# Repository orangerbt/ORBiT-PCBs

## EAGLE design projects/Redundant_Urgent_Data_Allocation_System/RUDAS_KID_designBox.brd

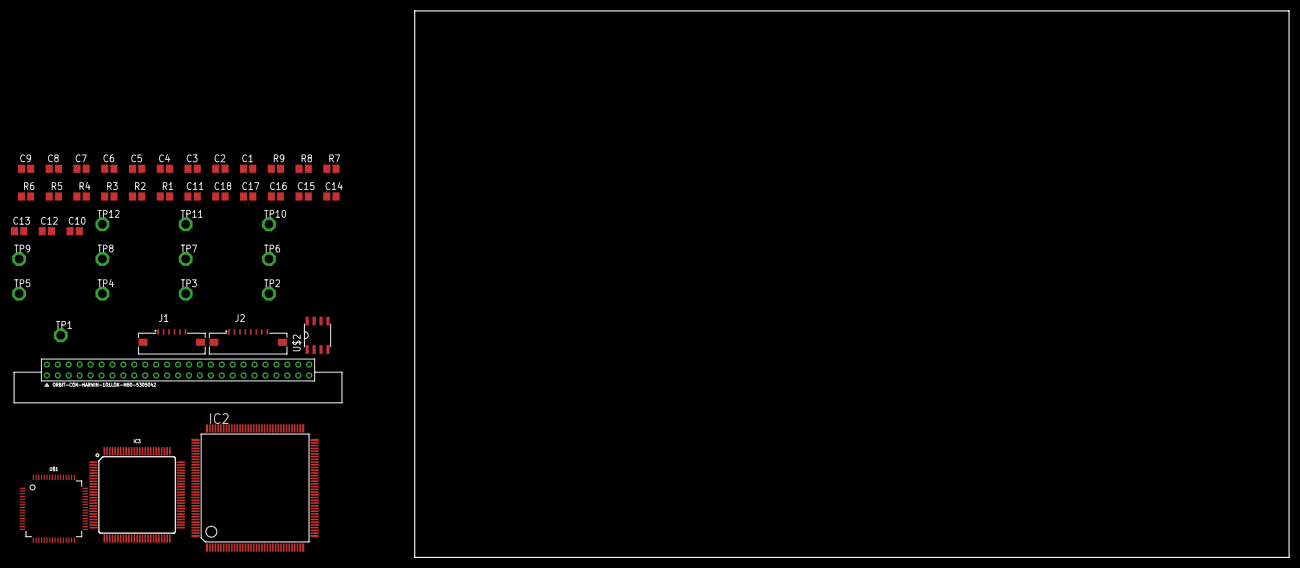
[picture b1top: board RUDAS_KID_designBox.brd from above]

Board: 2 copper layers, 160.0 x 100.0 mm, 46 parts (0 on the bottom side), 100 nets, no tracks yet.

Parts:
C1, C2, C3, C4, C5, C6, C7, C8, C9, C10, C11, C12, C13, C14, C15, C16, C17, C18: C2012
IC2: STM32F103VGT6; LQFP144
IC3: 5M240ZT100; TQFP100
J1: 686106183522
J2: 686108183422
R1, R2, R3, R4, R5, R6, R7, R8, R9: R2012
TP1, TP2, TP3, TP4, TP5, TP6, TP7, TP8, TP9, TP10, TP11, TP12: TP063; TP_063
U$1: IDT71V30; TQFP64
U$2: ISO1050; SOP8
U$5: CARD_EDGE_50PINM80-5305042; M80-5305042

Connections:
!BUSY!: IC3.77, U$1.60
!CE!: IC3.75, U$1.58
!INT!: IC3.76, U$1.61
!OE!: IC3.74, U$1.1
A0: IC3.73, U$1.2
A1: IC3.72, U$1.3
A2: IC3.71, U$1.4
A3: IC3.70, U$1.5
A4: IC3.69, U$1.6
A5: IC3.68, U$1.7
A6: IC3.67, U$1.8
A7: IC3.66, U$1.10
A8: IC3.64, U$1.11
A9: IC3.62, U$1.12
CPLD_GND: C3.2, C4.2, C5.2, C6.2, C7.2, C8.2, C9.2, C10.2, IC3.1, IC3.10, IC3.11, IC3.32, IC3.46, IC3.60, IC3.65, IC3.79, IC3.93, J1.1, R9.1
CPLD_IO_VCC: J1.6, R6.2, R7.2, R8.2
CPLD_VCC: C3.1, C4.1, C5.1, C6.1, C7.1, C8.1, C9.1, C10.1
CPLD_VCC_CORE: IC3.13, IC3.63
CPLD_VCC_IO2: IC3.59, IC3.80, IC3.94
CPL_VCC_IO1: IC3.9, IC3.31, IC3.45
C_TCK: IC3.24, J1.5, R9.2
C_TDI: IC3.23, J1.2, R8.1
C_TDO: IC3.25, J1.4, R6.1
C_TMS: IC3.22, J1.3, R7.1
D0: IC3.58, U$1.14
D1: IC3.57, U$1.15
D2: IC3.56, U$1.16
D3: IC3.55, U$1.17
D4: IC3.54, U$1.19
D5: IC3.53, U$1.20
D6: IC3.52, U$1.21
D7: IC3.51, U$1.22
FSMC_!NE1!: IC2.123, U$1.55
FSMC_!NOE!: IC2.118, U$1.48
FSMC_A0: IC2.10, U$1.47
FSMC_A1: IC2.11, U$1.46
FSMC_A2: IC2.12, U$1.45
FSMC_A3: IC2.13, U$1.44
FSMC_A4: IC2.14, U$1.43
FSMC_A5: IC2.15, U$1.42
FSMC_A6: IC2.50, U$1.41
FSMC_A7: IC2.53, U$1.39
FSMC_A8: IC2.54, U$1.38
FSMC_A9: IC2.55, U$1.37
FSMC_D0: IC2.85, U$1.26
FSMC_D1: IC2.86, U$1.27
FSMC_D2: IC2.114, U$1.28
FSMC_D3: IC2.115, U$1.29
FSMC_D4: IC2.58, U$1.31
FSMC_D5: IC2.59, U$1.32
FSMC_D6: IC2.60, U$1.33
FSMC_D7: IC2.63, U$1.34
LAN_CLK_N0: IC3.81, U$5.PIN9
LAN_CLK_N1: IC3.85, U$5.PIN15
LAN_CLK_N2: IC3.96, U$5.PIN21
LAN_CLK_N3: IC3.29, U$5.PIN34
LAN_CLK_N4: IC3.19, U$5.PIN40
LAN_CLK_N5: IC3.5, U$5.PIN46
LAN_CLK_P0: IC3.82, U$5.PIN10
LAN_CLK_P1: IC3.86, U$5.PIN16
LAN_CLK_P2: IC3.97, U$5.PIN22
LAN_CLK_P3: IC3.28, U$5.PIN35
LAN_CLK_P4: IC3.18, U$5.PIN41
LAN_CLK_P5: IC3.4, U$5.PIN47
LAN_N0: IC3.83, U$5.PIN11
LAN_N1: IC3.87, U$5.PIN17
LAN_N2: IC3.98, U$5.PIN23
LAN_N3: IC3.27, U$5.PIN36
LAN_N4: IC3.17, U$5.PIN42
LAN_N5: IC3.3, U$5.PIN48
LAN_P0: IC3.84, U$5.PIN12
LAN_P1: IC3.88, U$5.PIN18
LAN_P2: IC3.99, U$5.PIN24
LAN_P3: IC3.26, U$5.PIN37
LAN_P4: IC3.16, U$5.PIN43
LAN_P5: IC3.2, U$5.PIN49
unnamed: C1.1, C2.1, U$1.56, U$1.57
unnamed: C1.2, C2.2, U$1.24, U$1.25
R/!W!: IC3.78, U$1.59
SIGNAL_GND: U$5.PIN8, U$5.PIN14, U$5.PIN20, U$5.PIN33, U$5.PIN39, U$5.PIN45
STM32_CAN_RX: IC2.103, TP7.TP, U$2.2
STM32_CAN_TX: IC2.104, TP8.TP, U$2.3
STM32_I2C1_SCL: IC2.136, TP9.TP
STM32_I2C1_SDA: IC2.137, TP10.TP
STM32_SPI1_CS: IC2.40, TP1.TP
STM32_SPI1_MISO: IC2.42, TP3.TP
STM32_SPI1_MOSI: IC2.43, TP4.TP
STM32_SPI1_SCK: IC2.41, TP2.TP
STM32_UART1_RX: IC2.102, TP6.TP
STM32_UART1_TX: IC2.101, TP5.TP
STM32_UART2_RX: IC2.36, TP12.TP
STM32_UART2_TX: IC2.35, TP11.TP
S_GND: C11.2, C12.2, C13.2, C14.2, C15.2, C16.2, C17.2, C18.2, IC2.16, IC2.38, IC2.51, IC2.61, IC2.71, IC2.83, IC2.94, IC2.107, IC2.120, IC2.130, IC2.143, J2.1, R5.1, U$2.4
S_RST: IC2.25, J2.2
S_TCK: IC2.109, J2.4, R5.2
S_TDI: IC2.110, J2.6, R2.1
S_TDO: IC2.133, J2.3, R4.1
S_TMS: IC2.105, J2.5, R3.1
S_TRST: IC2.134, J2.7, R1.1
S_VCC: C11.1, C12.1, C13.1, C14.1, C15.1, C16.1, C17.1, C18.1, IC2.17, IC2.39, IC2.52, IC2.62, IC2.72, IC2.84, IC2.95, IC2.108, IC2.121, IC2.131, IC2.144, J2.8, R1.2, R2.2, R3.2, R4.2, U$2.1

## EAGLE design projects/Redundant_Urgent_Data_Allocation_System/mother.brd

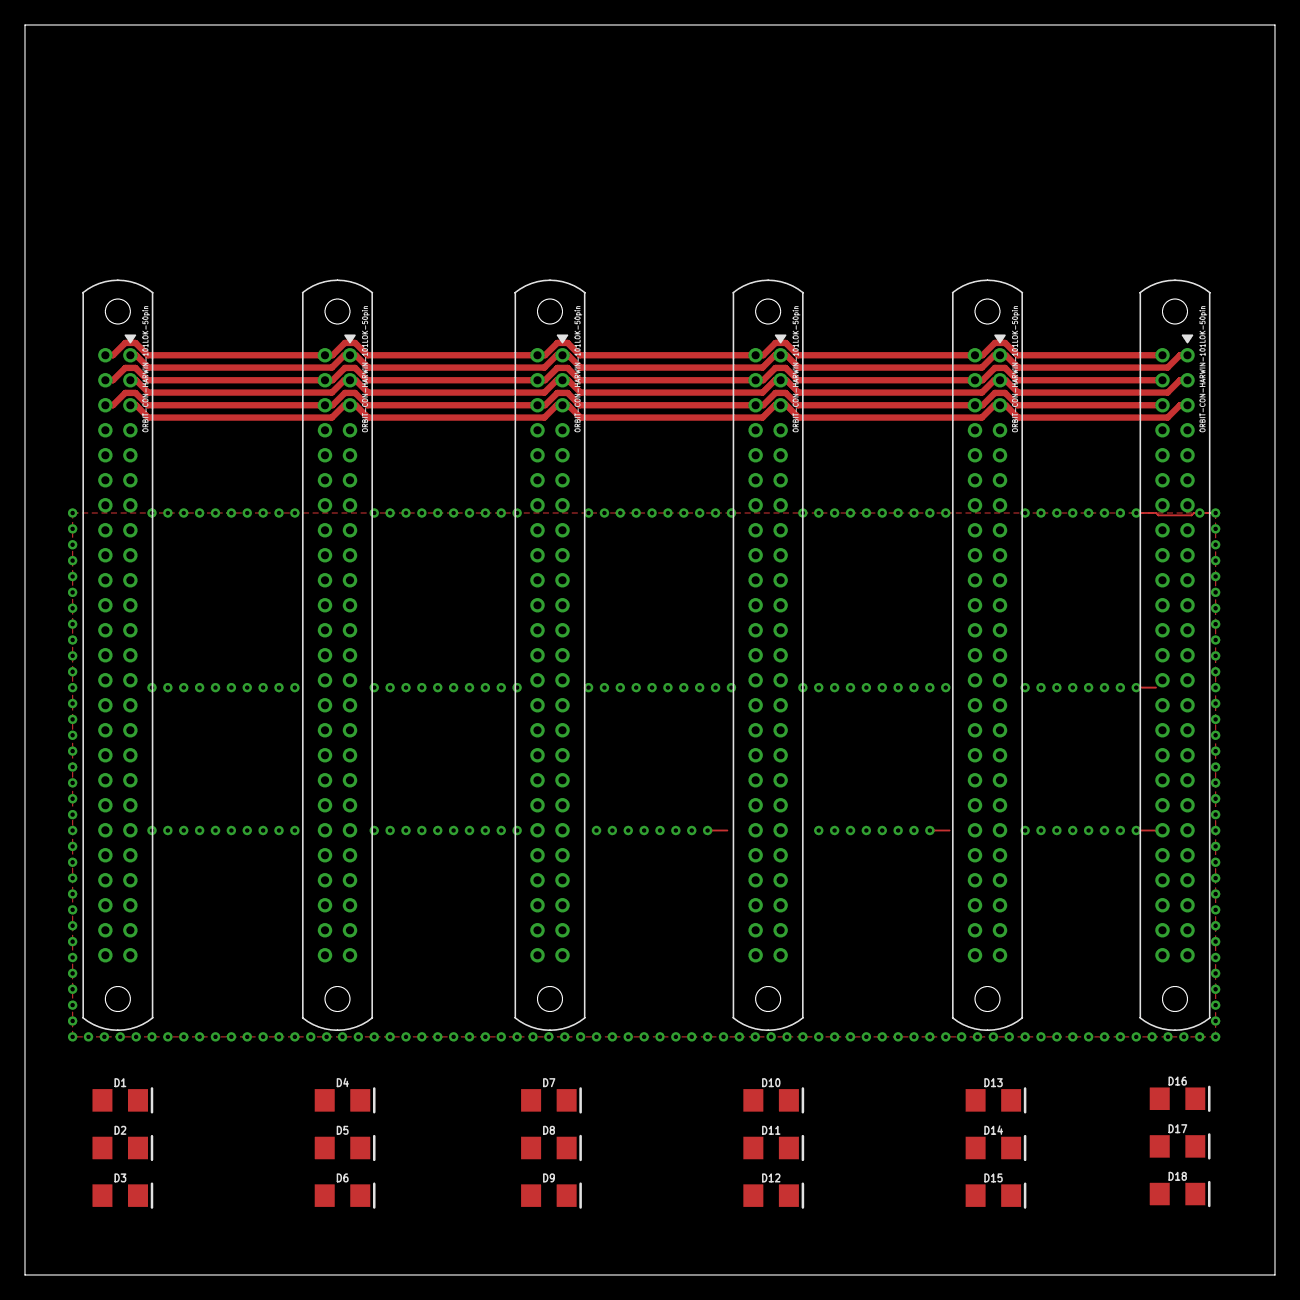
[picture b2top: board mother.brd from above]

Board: 4 copper layers, 100.0 x 100.0 mm, 24 parts (0 on the bottom side), 41 nets.

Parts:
D1, D2, D3, D4, D5, D6, D7, D8, D9, D10, D11, D12, D13, D14, D15, D16, D17, D18: FKIT-LED-1206
U$1, U$2, U$3, U$4, U$5, U$6: CARD_EDGE_50PINM80-4115042; M80-4115042

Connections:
3V_GND: U$1.PIN28, U$2.PIN28, U$3.PIN28, U$4.PIN28, U$5.PIN28, U$6.PIN28
5V_GND: U$1.PIN2, U$2.PIN2, U$3.PIN2, U$4.PIN2, U$5.PIN2, U$6.PIN2
12V_GND: U$1.PIN26, U$2.PIN26, U$3.PIN26, U$4.PIN26, U$5.PIN26, U$6.PIN26
+3V: U$1.PIN3, U$2.PIN3, U$3.PIN3, U$4.PIN3, U$5.PIN3, U$6.PIN3
+5V: U$1.PIN27, U$2.PIN27, U$3.PIN27, U$4.PIN27, U$5.PIN27, U$6.PIN27
+12V: U$1.PIN1, U$2.PIN1, U$3.PIN1, U$4.PIN1, U$5.PIN1, U$6.PIN1
CAN_H_P: U$1.PIN4, U$2.PIN4, U$3.PIN4, U$4.PIN4, U$5.PIN4, U$6.PIN4
CAN_H_S: U$1.PIN29, U$2.PIN29, U$3.PIN29, U$4.PIN29, U$5.PIN29, U$6.PIN29
CAN_L_P: U$1.PIN5, U$2.PIN5, U$3.PIN5, U$4.PIN5, U$5.PIN5, U$6.PIN5
CAN_L_S: U$1.PIN30, U$2.PIN30, U$3.PIN30, U$4.PIN30, U$5.PIN30, U$6.PIN30
LAN_CLK_N0: U$1.PIN9, U$2.PIN9, U$3.PIN9, U$4.PIN9, U$5.PIN9, U$6.PIN9
LAN_CLK_N1: U$1.PIN15, U$2.PIN15, U$3.PIN15, U$4.PIN15, U$5.PIN15, U$6.PIN15
LAN_CLK_N2: U$1.PIN21, U$2.PIN21, U$3.PIN21, U$4.PIN21, U$5.PIN21, U$6.PIN21
LAN_CLK_N3: U$1.PIN34, U$2.PIN34, U$3.PIN34, U$4.PIN34, U$5.PIN34, U$6.PIN34
LAN_CLK_N4: U$1.PIN40, U$2.PIN40, U$3.PIN40, U$4.PIN40, U$5.PIN40, U$6.PIN40
LAN_CLK_N5: U$1.PIN46, U$2.PIN46, U$3.PIN46, U$4.PIN46, U$5.PIN46, U$6.PIN46
LAN_CLK_P0: U$1.PIN10, U$2.PIN10, U$3.PIN10, U$4.PIN10, U$5.PIN10, U$6.PIN10
LAN_CLK_P1: U$1.PIN16, U$2.PIN16, U$3.PIN16, U$4.PIN16, U$5.PIN16, U$6.PIN16
LAN_CLK_P2: U$1.PIN22, U$2.PIN22, U$3.PIN22, U$4.PIN22, U$5.PIN22, U$6.PIN22
LAN_CLK_P3: U$1.PIN35, U$2.PIN35, U$3.PIN35, U$4.PIN35, U$5.PIN35, U$6.PIN35
LAN_CLK_P4: U$1.PIN41, U$2.PIN41, U$3.PIN41, U$4.PIN41, U$5.PIN41, U$6.PIN41
LAN_CLK_P5: U$1.PIN47, U$2.PIN47, U$3.PIN47, U$4.PIN47, U$5.PIN47, U$6.PIN47
LAN_N0: U$1.PIN11, U$2.PIN11, U$3.PIN11, U$4.PIN11, U$5.PIN11, U$6.PIN11
LAN_N1: U$1.PIN17, U$2.PIN17, U$3.PIN17, U$4.PIN17, U$5.PIN17, U$6.PIN17
LAN_N2: U$1.PIN23, U$2.PIN23, U$3.PIN23, U$4.PIN23, U$5.PIN23, U$6.PIN23
LAN_N3: U$1.PIN36, U$2.PIN36, U$3.PIN36, U$4.PIN36, U$5.PIN36, U$6.PIN36
LAN_N4: U$1.PIN42, U$2.PIN42, U$3.PIN42, U$4.PIN42, U$5.PIN42, U$6.PIN42
LAN_N5: U$1.PIN48, U$2.PIN48, U$3.PIN48, U$4.PIN48, U$5.PIN48, U$6.PIN48
LAN_P0: U$1.PIN12, U$2.PIN12, U$3.PIN12, U$4.PIN12, U$5.PIN12, U$6.PIN12
LAN_P1: U$1.PIN18, U$2.PIN18, U$3.PIN18, U$4.PIN18, U$5.PIN18, U$6.PIN18
LAN_P2: U$1.PIN24, U$2.PIN24, U$3.PIN24, U$4.PIN24, U$5.PIN24, U$6.PIN24
LAN_P3: U$1.PIN37, U$2.PIN37, U$3.PIN37, U$4.PIN37, U$5.PIN37, U$6.PIN37
LAN_P4: U$1.PIN43, U$2.PIN43, U$3.PIN43, U$4.PIN43, U$5.PIN43, U$6.PIN43
LAN_P5: U$1.PIN49, U$2.PIN49, U$3.PIN49, U$4.PIN49, U$5.PIN49, U$6.PIN49
NOTE0: U$1.PIN13, U$2.PIN13, U$3.PIN13, U$4.PIN13, U$5.PIN13, U$6.PIN13
NOTE1: U$1.PIN19, U$2.PIN19, U$3.PIN19, U$4.PIN19, U$5.PIN19, U$6.PIN19
NOTE2: U$1.PIN25, U$2.PIN25, U$3.PIN25, U$4.PIN25, U$5.PIN25, U$6.PIN25
NOTE3: U$1.PIN38, U$2.PIN38, U$3.PIN38, U$4.PIN38, U$5.PIN38, U$6.PIN38
NOTE4: U$1.PIN44, U$2.PIN44, U$3.PIN44, U$4.PIN44, U$5.PIN44, U$6.PIN44
NOTE5: U$1.PIN50, U$2.PIN50, U$3.PIN50, U$4.PIN50, U$5.PIN50, U$6.PIN50
SIGNAL_GND: U$1.PIN8, U$1.PIN14, U$1.PIN20, U$1.PIN33, U$1.PIN39, U$1.PIN45, U$2.PIN8, U$2.PIN14, U$2.PIN20, U$2.PIN33, U$2.PIN39, U$2.PIN45, U$3.PIN8, U$3.PIN14, U$3.PIN20, U$3.PIN33, U$3.PIN39, U$3.PIN45, U$4.PIN8, U$4.PIN14, U$4.PIN20, U$4.PIN33, U$4.PIN39, U$4.PIN45, U$5.PIN8, U$5.PIN14, U$5.PIN20, U$5.PIN33, U$5.PIN39, U$5.PIN45, U$6.PIN8, U$6.PIN14, U$6.PIN20, U$6.PIN33, U$6.PIN39, U$6.PIN45

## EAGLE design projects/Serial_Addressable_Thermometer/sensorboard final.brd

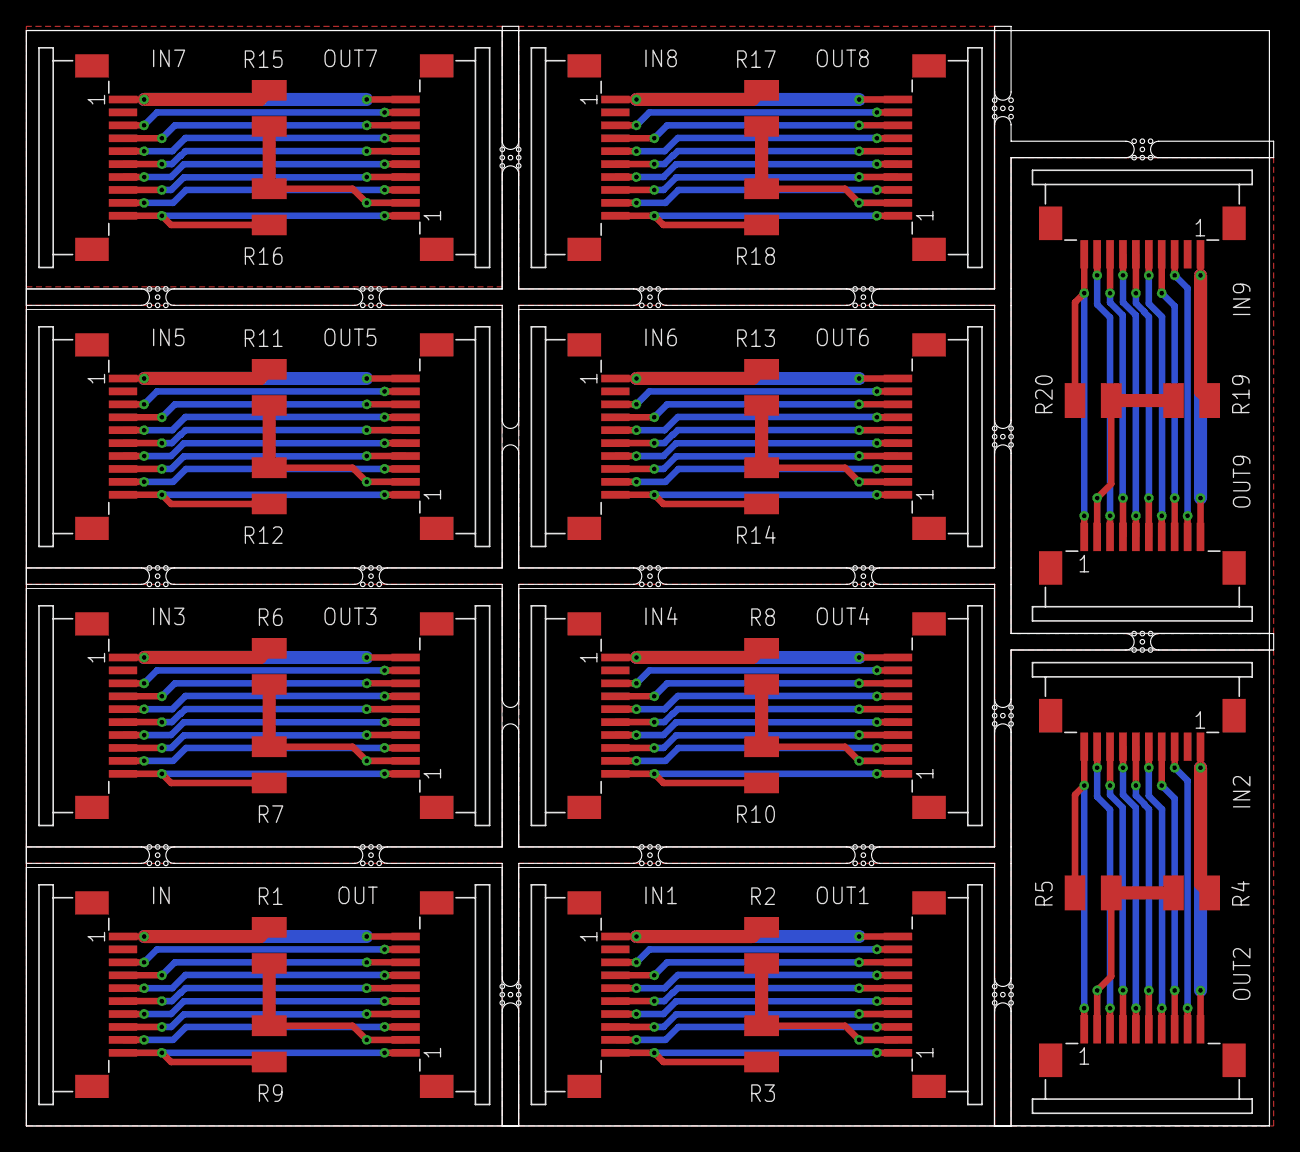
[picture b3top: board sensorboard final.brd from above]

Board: 2 copper layers, 96.2 x 84.8 mm, 40 parts (0 on the bottom side), 100 nets.

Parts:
IN, IN1, IN2, IN3, IN4, IN5, IN6, IN7, IN8, IN9: analog; 68611014422
OUT, OUT1, OUT2, OUT3, OUT4, OUT5, OUT6, OUT7, OUT8, OUT9: analog; 68611014422
R1, R2, R4, R6, R8, R11, R13, R15, R17, R19: NTC; R1210
R3, R5, R7, R9, R10, R12, R14, R16, R18, R20: 10K; R1210

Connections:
+5V: IN.1, OUT.10, R1.2
+5V1: IN1.1, OUT1.10, R2.2
+5V2: IN2.1, OUT2.10, R4.2
+5V3: IN3.1, OUT3.10, R6.2
+5V4: IN4.1, OUT4.10, R8.2
+5V5: IN5.1, OUT5.10, R11.2
+5V6: IN6.1, OUT6.10, R13.2
+5V7: IN7.1, OUT7.10, R15.2
+5V8: IN8.1, OUT8.10, R17.2
+5V9: IN9.1, OUT9.10, R19.2
AD1: IN1.3, OUT1.9
AD2: IN.3, OUT.9
AD3: IN.4, OUT.8
AD4: IN.5, OUT.7
AD5: IN.6, OUT.6
AD6: IN.7, OUT.5
AD7: IN.8, OUT.4
AD8: IN.9, OUT.3
AD9: IN1.4, OUT1.8
AD10: IN1.5, OUT1.7
AD11: IN1.9, OUT1.3
AD12: IN1.8, OUT1.4
AD13: IN1.7, OUT1.5
AD14: IN1.6, OUT1.6
AD15: IN2.3, OUT2.9
AD16: IN2.4, OUT2.8
AD17: IN2.5, OUT2.7
AD18: IN2.9, OUT2.3
AD19: IN2.8, OUT2.4
AD20: IN2.7, OUT2.5
AD21: IN2.6, OUT2.6
AD22: IN3.3, OUT3.9
AD23: IN3.4, OUT3.8
AD24: IN3.5, OUT3.7
AD25: IN3.9, OUT3.3
AD26: IN3.8, OUT3.4
AD27: IN3.7, OUT3.5
AD28: IN3.6, OUT3.6
AD29: IN4.3, OUT4.9
AD30: IN4.4, OUT4.8
AD31: IN4.5, OUT4.7
AD32: IN4.9, OUT4.3
AD33: IN4.8, OUT4.4
AD34: IN4.7, OUT4.5
AD35: IN4.6, OUT4.6
AD36: IN5.3, OUT5.9
AD37: IN5.4, OUT5.8
AD38: IN5.5, OUT5.7
AD39: IN5.9, OUT5.3
AD40: IN5.8, OUT5.4
AD41: IN5.7, OUT5.5
AD42: IN5.6, OUT5.6
AD43: IN6.3, OUT6.9
AD44: IN6.4, OUT6.8
AD45: IN6.5, OUT6.7
AD46: IN6.9, OUT6.3
AD47: IN6.8, OUT6.4
AD48: IN6.7, OUT6.5
AD49: IN6.6, OUT6.6
AD50: IN7.3, OUT7.9
AD51: IN7.4, OUT7.8
AD52: IN7.5, OUT7.7
AD53: IN7.9, OUT7.3
AD54: IN7.8, OUT7.4
AD55: IN7.7, OUT7.5
AD56: IN7.6, OUT7.6
AD57: IN8.3, OUT8.9
AD58: IN8.4, OUT8.8
AD59: IN8.5, OUT8.7
AD60: IN8.9, OUT8.3
AD61: IN8.8, OUT8.4
AD62: IN8.7, OUT8.5
AD63: IN8.6, OUT8.6
AD64: IN9.3, OUT9.9
AD65: IN9.4, OUT9.8
AD66: IN9.5, OUT9.7
AD67: IN9.9, OUT9.3
AD68: IN9.8, OUT9.4
AD69: IN9.7, OUT9.5
AD70: IN9.6, OUT9.6
ADB: OUT.2, R1.1, R9.2
ADB1: OUT1.2, R2.1, R3.2
ADB2: OUT2.2, R4.1, R5.2
ADB3: OUT3.2, R6.1, R7.2
ADB4: OUT4.2, R8.1, R10.2
ADB5: OUT5.2, R11.1, R12.2
ADB6: OUT6.2, R13.1, R14.2
ADB7: OUT7.2, R15.1, R16.2
ADB8: OUT8.2, R17.1, R18.2
ADB9: OUT9.2, R19.1, R20.2
AGND: IN.10, OUT.1, R9.1
AGND1: IN1.10, OUT1.1, R3.1
AGND2: IN2.10, OUT2.1, R5.1
AGND3: IN3.10, OUT3.1, R7.1
AGND4: IN4.10, OUT4.1, R10.1
AGND5: IN5.10, OUT5.1, R12.1
AGND6: IN6.10, OUT6.1, R14.1
AGND7: IN7.10, OUT7.1, R16.1
AGND8: IN8.10, OUT8.1, R18.1
AGND9: IN9.10, OUT9.1, R20.1

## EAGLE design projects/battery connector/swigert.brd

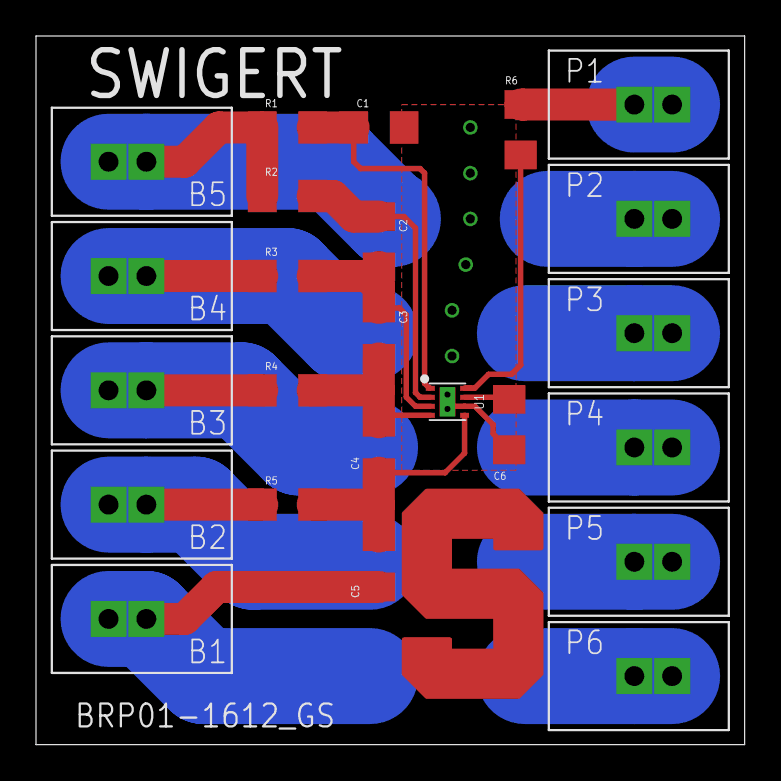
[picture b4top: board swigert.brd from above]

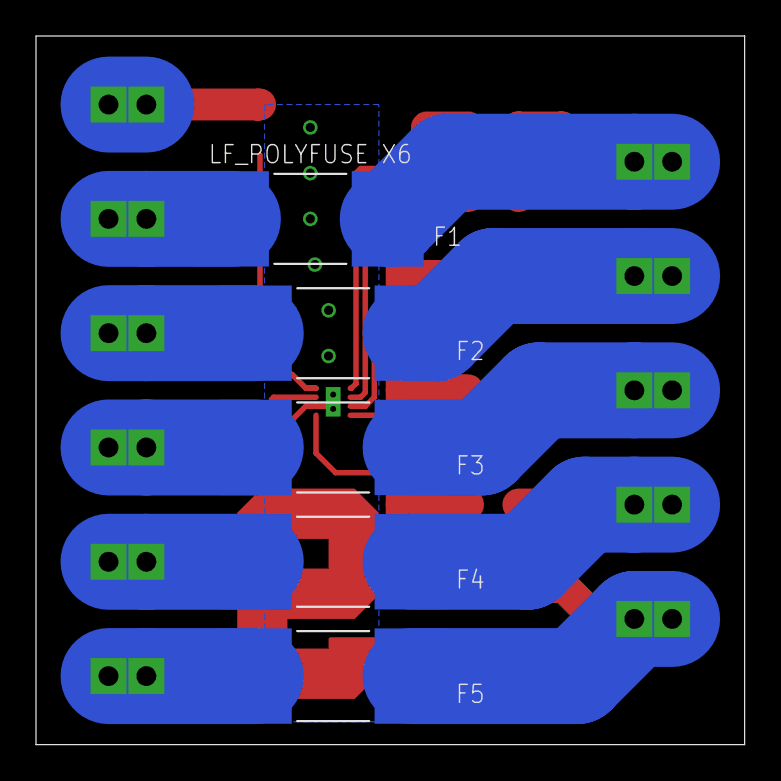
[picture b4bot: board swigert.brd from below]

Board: 2 copper layers, 39.4 x 39.4 mm, 30 parts (5 on the bottom side), 18 nets.

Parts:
B1, B2, B3, B4, B5: MOLEX_SRT; MOLEX_SRT_14-20
C1, C2, C3, C4, C5, C6: 0.1u; 1206
F1: LF_POLYFUSE X6; 2920
F2, F3, F4, F5: LF_POLYFUSE; 2920
LOGO: SU_LOGO-DUMMY2; SU_LOGO_SS
P1, P2, P3, P4, P5, P6: MOLEX_SRT; MOLEX_SRT_14-20
R1: 100; 1206
R2, R3, R4, R5: 1k; 1206
R6: 5.1k; 1206
U1: BQ294709; WSON8

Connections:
GND: B1.P$1, B1.P$2, C1.2, C5.2, C6.2, F5.P$1, U1.P$6, U1.P$9, U1.P$9_1, U1.P$9_2
unnamed: C1.1, R1.2, U1.P$1
unnamed: C2.1, R2.2, U1.P$2
unnamed: C2.2, C3.1, R3.2, U1.P$3
unnamed: C3.2, C4.1, R4.2, U1.P$4
unnamed: C4.2, C5.1, R5.2, U1.P$5
unnamed: F4.P$2, P5.P$1, P5.P$2
unnamed: B2.P$1, B2.P$2, F4.P$1, R5.1
unnamed: C6.1, U1.P$7
unnamed: B3.P$1, B3.P$2, F3.P$1, R4.1
unnamed: B4.P$1, B4.P$2, F2.P$1, R3.1
unnamed: B5.P$1, B5.P$2, F1.P$1, R1.1, R2.1
unnamed: R6.1, U1.P$8
unnamed: P1.P$1, P1.P$2, R6.2
unnamed: F3.P$2, P4.P$1, P4.P$2
unnamed: F2.P$2, P3.P$1, P3.P$2
unnamed: F1.P$2, P2.P$1, P2.P$2
unnamed: F5.P$2, P6.P$1, P6.P$2

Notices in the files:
parts and their libraries:
Wurth_Elektronik_Electromechanic_FPC_Con: Copyright: Würth Elektronik
SparkFun-LED: Licensing: Creative Commons ShareAlike 4.0 International - https://creativecommons.org/licenses/by-sa/4.0
